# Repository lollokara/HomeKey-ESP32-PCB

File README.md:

<div align="center">

# HomeKey-ESP32-PCB

**A miniaturized, wall-mountable HomeKey reader board**

A custom PCB implementation of [rednblkx/HomeKey-ESP32](https://github.com/rednblkx/HomeKey-ESP32) that brings Apple HomeKey NFC unlocking into a form factor small enough to hide behind your existing wall plate.

</div>

## What is this?

This project is a **hardware redesign** of the excellent [HomeKey-ESP32](https://github.com/rednblkx/HomeKey-ESP32) firmware by [@rednblkx](https://github.com/rednblkx). Instead of using a separate development board wired to a breakout PN532 module, everything is integrated onto a single, compact PCB.

The board packs an **ESP32-C3** and an **NFC reader front-end with an on-board coaxial NFC antenna** into a footprint designed to fit inside a **European 503 (3-module) flush-mount wall box**. This lets you install a fully functional Apple HomeKey reader directly behind a standard wall plate — no external modules, no messy wiring.

## Key Highlights

- **All-in-one PCB** — ESP32-C3 + NFC front-end + coaxial antenna on a single board
- **Fits a European 503 plug slot** — designed for standard flush-mount wall boxes
- **Integrated coaxial NFC antenna** — tuned on-board antenna, no external coil needed
- **Runs the original HomeKey-ESP32 firmware** — full Apple HomeKey / HomeKit compatibility
- **Fully open hardware** — designed in **KiCad**, with schematics, layout, Gerbers and a 3D model included

## Get the Board

Don't want to fabricate it yourself? You can order the PCB directly from PCBWay:

**➡️ [ESP32 HomeKey on PCBWay](https://www.pcbway.com/project/shareproject/ESP32_Homekey_77a119d7.html)**

## Designed in KiCad

The entire board is designed with **[KiCad](https://www.kicad.org/)**, so the complete hardware source is open and editable. The repository includes:

- Hierarchical KiCad schematics (`Homekey.kicad_sch`, `ESP32.kicad_sch`, `NFC.kicad_sch`, `Power.kicad_sch`, `Square.kicad_sch`)
- KiCad PCB layout (`Homekey.kicad_pcb`) and project file (`Homekey.kicad_pro`)
- Exported schematic PDF (`Homekey.pdf`)
- Bill of Materials (`Homekey.xlsx`)
- A 3D model of the assembly (`Homekey 3D.step.zip`)

You can open the project directly in KiCad to review, modify, or re-fabricate the board.

## Repository Structure

```
HomeKey-ESP32-PCB/
├── Firmware/              # HomeKey-ESP32 firmware (based on the original repo)
├── Gerbers/               # Fabrication-ready Gerber files
├── ESP32.kicad_sch        # ESP32-C3 subsheet
├── NFC.kicad_sch          # NFC front-end + antenna subsheet
├── Power.kicad_sch        # Power supply subsheet
├── Square.kicad_sch       # Additional subsheet
├── Homekey.kicad_sch      # Top-level schematic
├── Homekey.kicad_pcb      # PCB layout
├── Homekey.kicad_pro      # KiCad project file
├── Homekey.pdf            # Schematic (PDF export)
├── Homekey.xlsx           # Bill of Materials
├── Homekey-job.gbrjob     # Gerber job file
├── Homekey 3D.step.zip    # 3D model of the board
├── Homekey-3D-render.png  # 3D render of the assembled board
└── README.md
```

## Getting Started

### 1. Get the Board

- **Buy it ready-made:** order the PCB directly from [PCBWay](https://www.pcbway.com/project/shareproject/ESP32_Homekey_77a119d7.html).
- **Fabricate it yourself:** use the ready-to-order files in the [`Gerbers`](Gerbers) folder with your preferred PCB fab house.
- Refer to `Homekey.xlsx` for the Bill of Materials and `Homekey.pdf` for the schematic.
- To modify the design first, open `Homekey.kicad_pro` in KiCad.

### 2. Flash the Firmware

The board runs the standard HomeKey-ESP32 firmware. The [`Firmware`](Firmware) folder contains a build based on the original repository.

```bash
# Install esptool (one-time setup)
pip install esptool

# Flash the firmware (replace YOUR_PORT)
esptool.py --port YOUR_PORT write_flash 0x0 firmware.factory.bin
```

> Prefer a GUI? Use the [browser-based flasher](https://espressif.github.io/esptool-js/) — no command line needed.

For firmware configuration, pairing, and usage, follow the official documentation:
- **Docs:** https://rednblkx.github.io/HomeKey-ESP32/
- **Upstream firmware:** https://github.com/rednblkx/HomeKey-ESP32

### 3. Install & Pair

1. Mount the board inside your 503 wall box behind the plate.
2. Connect to the device's setup WiFi AP and configure your WiFi + HomeKit setup code.
3. Pair with Apple Home and start unlocking with a tap of your iPhone or Apple Watch. 🎉

## Credits

- **[@rednblkx](https://github.com/rednblkx)** — creator of the original [HomeKey-ESP32](https://github.com/rednblkx/HomeKey-ESP32) firmware this board is built for
- **[@kormax](https://github.com/kormax)** — reverse-engineered the HomeKey NFC protocol
- **[@kupa22](https://github.com/kupa22)** — researched the HAP side of HomeKey

## License

This project is licensed under the **MIT License** — see the [LICENSE](LICENSE) file for details.

## Disclaimer

This project implements Apple HomeKey functionality through reverse engineering.

- **Not affiliated** with, nor condoned by, Apple Inc.
- **Use at your own risk** for security-critical applications.
- **Apple**, **iPhone**, and **Apple Watch** are trademarks of Apple Inc.
- **ESP32** is a trademark of Espressif Systems (Shanghai) Co., Ltd.

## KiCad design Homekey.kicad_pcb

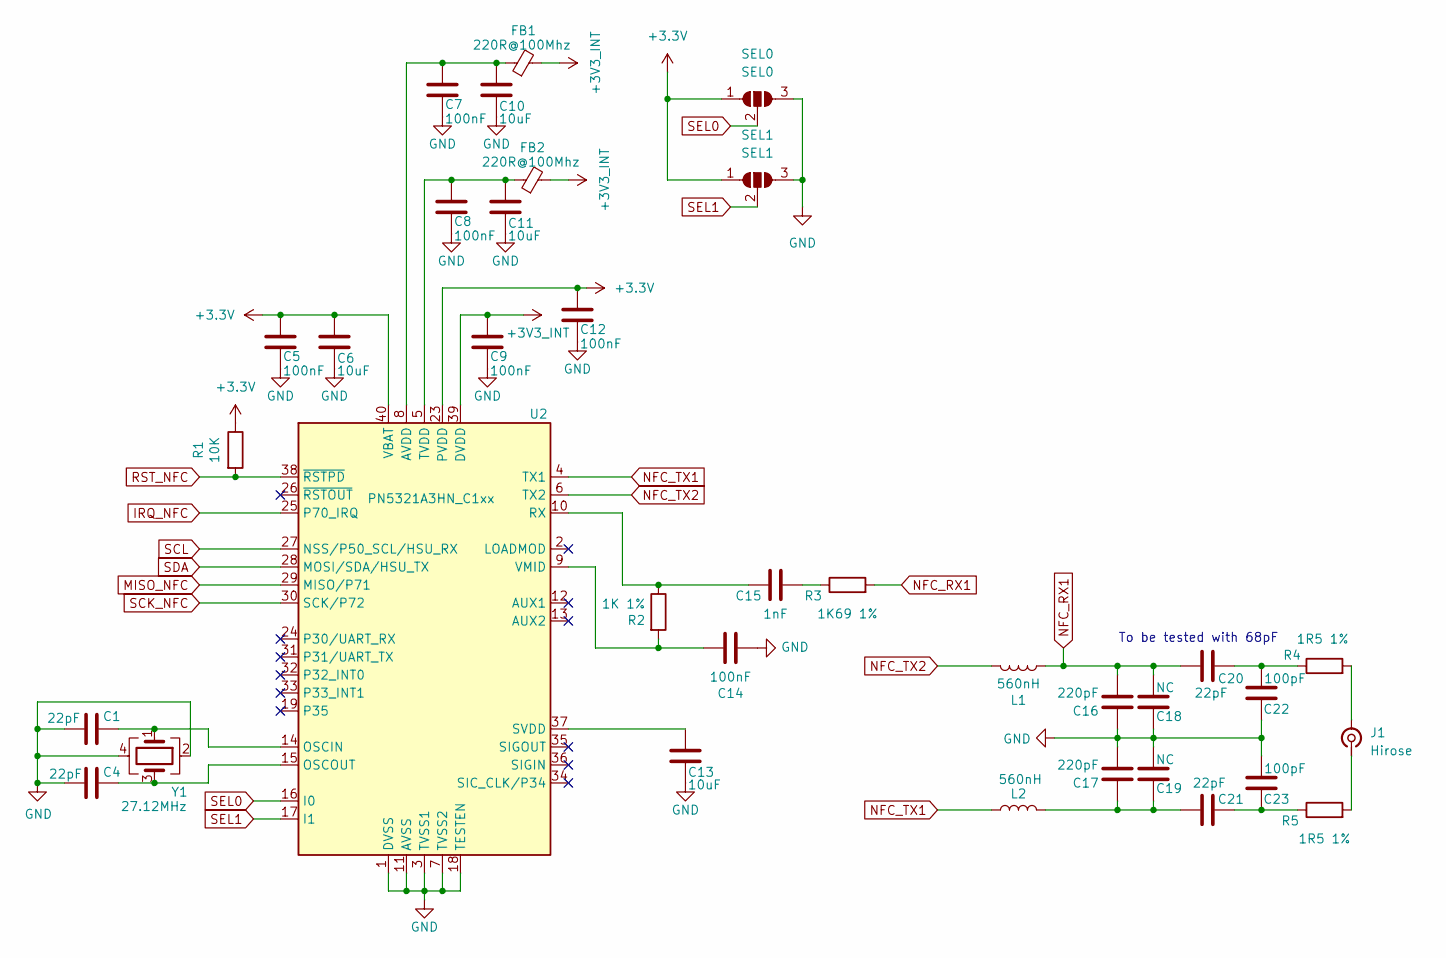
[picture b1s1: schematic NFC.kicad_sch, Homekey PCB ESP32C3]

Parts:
C1, C4: 22pF; C_0603_1608Metric; Part No 0603-22pF-50V
C5, C7, C8, C9, C12: 100nF; C_0603_1608Metric
C6, C10, C11, C13: 10uF; C_0805_2012Metric
C14: 100nF; C_0603_1608Metric; Part No 0603-100nF-25V
C15: 1nF; C_0603_1608Metric; Part No VJ0603A102GXAPW1BC
C16, C17: 220pF; C_0603_1608Metric; Part No 0603-220pF-50V
C18, C19: NC; C_0603_1608Metric
C20, C21: 22pF; C_0603_1608Metric; Part No 0603N220F500CT
C22, C23: 100pF; C_0603_1608Metric; Part No 0603-100pF-50V
FB1, FB2: 220R@100Mhz; L_0603_1608Metric
J1: Hirose; U.FL_Hirose_U.FL-R-SMT-1_Vertical
L1, L2: 560nH; L_0805_2012Metric; Part No LQW2UASR56G00L
R1: 10K; R_0603_1608Metric; Part No 0603-10K
R2: 1K 1%; R_0603_1608Metric; Part No CRCW06031K00FKEAC
R3: 1K69 1%; R_0603_1608Metric; Part No RC0603FR-101K69L
R4, R5: 1R5 1%; R_0603_1608Metric; Part No CRCW06031R50FKEA
SEL0: SEL0; SolderJumper-3_P2.0mm_Open_TrianglePad1.0x1.5mm
SEL1: SEL1; SolderJumper-3_P2.0mm_Open_TrianglePad1.0x1.5mm
U2: PN5321A3HN_C1xx; HVQFN-40-1EP_6x6mm_P0.5mm_EP4.1x4.1mm
Y1: 27.12MHz; Crystal_SMD_3225-4Pin_3.2x2.5mm; Part No ABM81-27.120MHZ-10-B1U-T3

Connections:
+3.3V: C5.2, C6.1, C12.2, R1.1, SEL0.1 (A), SEL1.1 (A), U2.23 (PVDD), U2.40 (VBAT); also elsewhere on the board
+3V3_INT: C9.2, FB1.2, FB2.2, U2.39 (DVDD)
GND: C1.2, C4.2, C5.1, C6.2, C7.1, C8.1, C9.1, C10.2, C11.2, C12.1, C13.2, C14.2, C16.1, C17.1, C18.1, C19.2, C22.1, C23.2, SEL0.3 (B), SEL1.3 (B), U2.1 (DVSS), U2.3 (TVSS1), U2.7 (TVSS2), U2.11 (AVSS), U2.18 (TESTEN), U2.41 (AVSS), Y1.2, Y1.4; also elsewhere on the board
IRQ_NFC: U2.25 (P70_IRQ); also elsewhere on the board
MISO_NFC: U2.29 (MISO/P71); also elsewhere on the board
NFC_RX1: C16.2, C18.2, C20.1, L1.1, R3.2
NFC_TX1: L2.1, U2.4 (TX1)
NFC_TX2: L1.2, U2.6 (TX2)
unnamed: C15.2, R3.1
unnamed: C17.2, C19.1, C21.1, L2.2
unnamed: C20.2, C22.2, R4.1
unnamed: C21.2, C23.1, R5.1
unnamed: J1.2 (Ext), R4.2
unnamed: J1.1 (In), R5.2
unnamed: C7.2, C10.1, FB1.1, U2.8 (AVDD)
unnamed: C1.1, U2.14 (OSCIN), Y1.1
unnamed: C4.1, U2.15 (OSCOUT), Y1.3
unnamed: C15.1, R2.1, U2.10 (RX)
unnamed: C13.1, U2.37 (SVDD)
unnamed: C8.2, C11.1, FB2.1, U2.5 (TVDD)
unnamed: C14.1, R2.2, U2.9 (VMID)
RST_NFC: R1.2, U2.38 (~RSTPD); also elsewhere on the board
SCK_NFC: U2.30 (SCK/P72); also elsewhere on the board
SCL: U2.27 (NSS/P50_SCL/HSU_RX); also elsewhere on the board
SDA: U2.28 (MOSI/SDA/HSU_TX); also elsewhere on the board
SEL0: SEL0.2 (C), U2.16 (I0)
SEL1: SEL1.2 (C), U2.17 (I1)

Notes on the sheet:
To be tested with 68pF

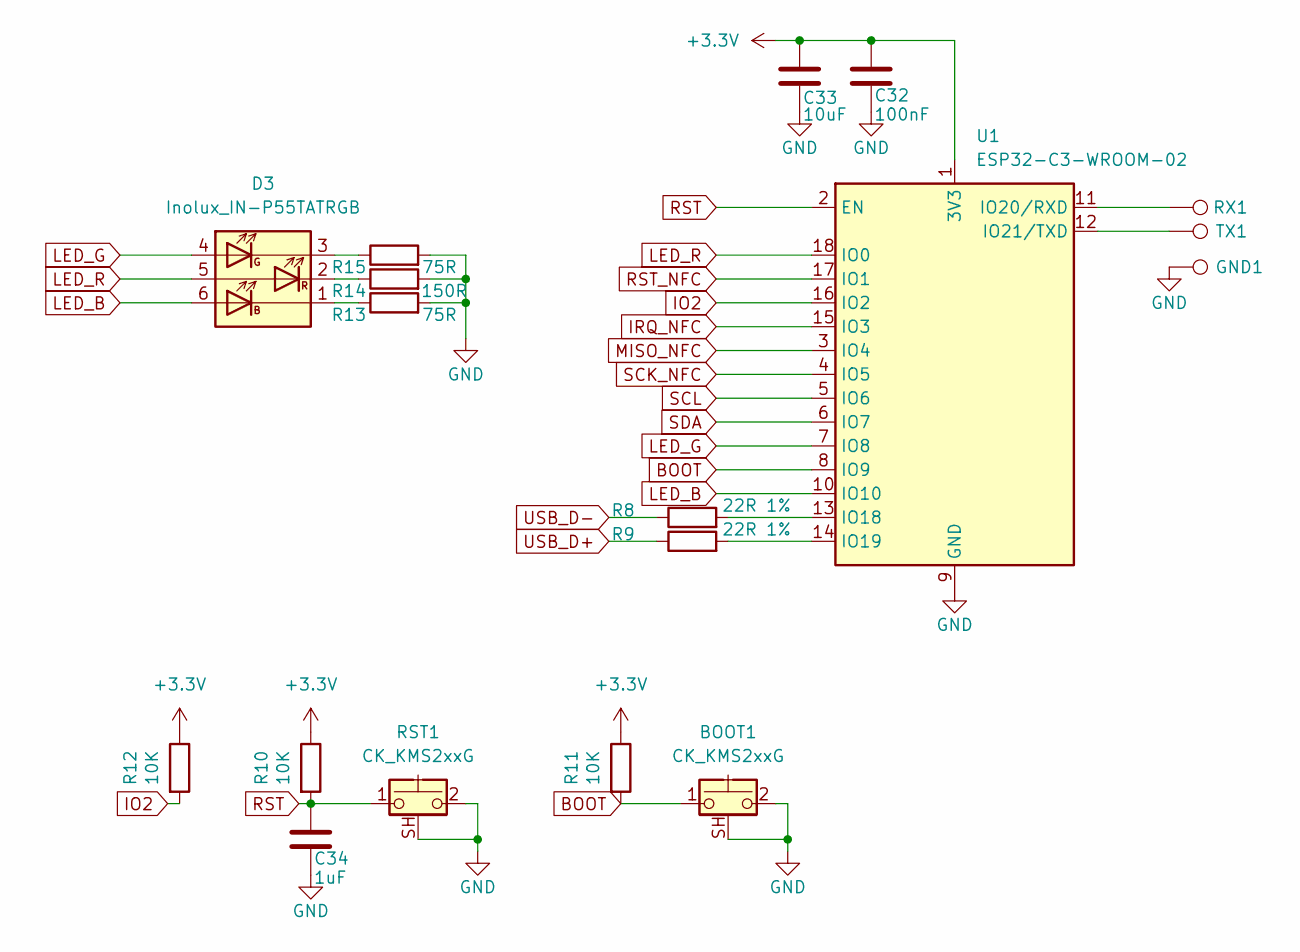
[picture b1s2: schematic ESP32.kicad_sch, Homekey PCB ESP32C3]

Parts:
BOOT1: CK_KMS2xxG; SW_SPST_CK_KMS2xxGP
C32: 100nF; C_0603_1608Metric
C33: 10uF; C_0805_2012Metric
C34: 1uF; C_0603_1608Metric
D3: Inolux_IN-P55TATRGB; LED_Inolux_IN-P55TATRGB_PLCC6_5.0x5.5mm_P1.8mm
GND1: TestPoint; TestPoint_THTPad_1.5x1.5mm_Drill0.7mm
R8, R9: 22R 1%; R_0603_1608Metric; Part No RC0603FR-1022RL
R10, R11, R12: 10K; R_0603_1608Metric; Part No 0603-10K
R13, R15: 75R; R_0603_1608Metric; Part No RC0603FR-0775RL
R14: 150R; R_0603_1608Metric; Part No RC0603JR-07160RL
RST1: CK_KMS2xxG; SW_SPST_CK_KMS2xxGP
RX1: TestPoint; TestPoint_THTPad_1.5x1.5mm_Drill0.7mm
TX1: TestPoint; TestPoint_THTPad_1.5x1.5mm_Drill0.7mm
U1: ESP32-C3-WROOM-02

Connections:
+3.3V: C32.2, C33.1, R10.1, R11.1, R12.1, U1.1 (3V3); also elsewhere on the board
BOOT: BOOT1.1, R11.2, U1.8 (IO9)
GND: BOOT1.2, BOOT1.SH (B), C32.1, C33.2, C34.1, GND1.1, R13.2, R14.2, R15.2, RST1.2, RST1.SH (B), U1.9 (GND), U1.19 (GND); also elsewhere on the board
IO2: R12.2, U1.16 (IO2)
IRQ_NFC: U1.15 (IO3); also elsewhere on the board
LED_B: D3.6 (AB), U1.10 (IO10)
LED_G: D3.4 (AG), U1.7 (IO8)
LED_R: D3.5 (AR), U1.18 (IO0)
MISO_NFC: U1.3 (IO4); also elsewhere on the board
unnamed: D3.1 (KB), R13.1
unnamed: D3.3 (KG), R15.1
unnamed: D3.2 (KR), R14.1
unnamed: R8.2, U1.13 (IO18)
unnamed: R9.2, U1.14 (IO19)
unnamed: RX1.1, U1.11 (IO20/RXD)
unnamed: TX1.1, U1.12 (IO21/TXD)
RST: C34.2, R10.2, RST1.1, U1.2 (EN)
RST_NFC: U1.17 (IO1); also elsewhere on the board
SCK_NFC: U1.4 (IO5); also elsewhere on the board
SCL: U1.5 (IO6); also elsewhere on the board
SDA: U1.6 (IO7); also elsewhere on the board
USB_D+: R9.1; also elsewhere on the board
USB_D-: R8.1; also elsewhere on the board

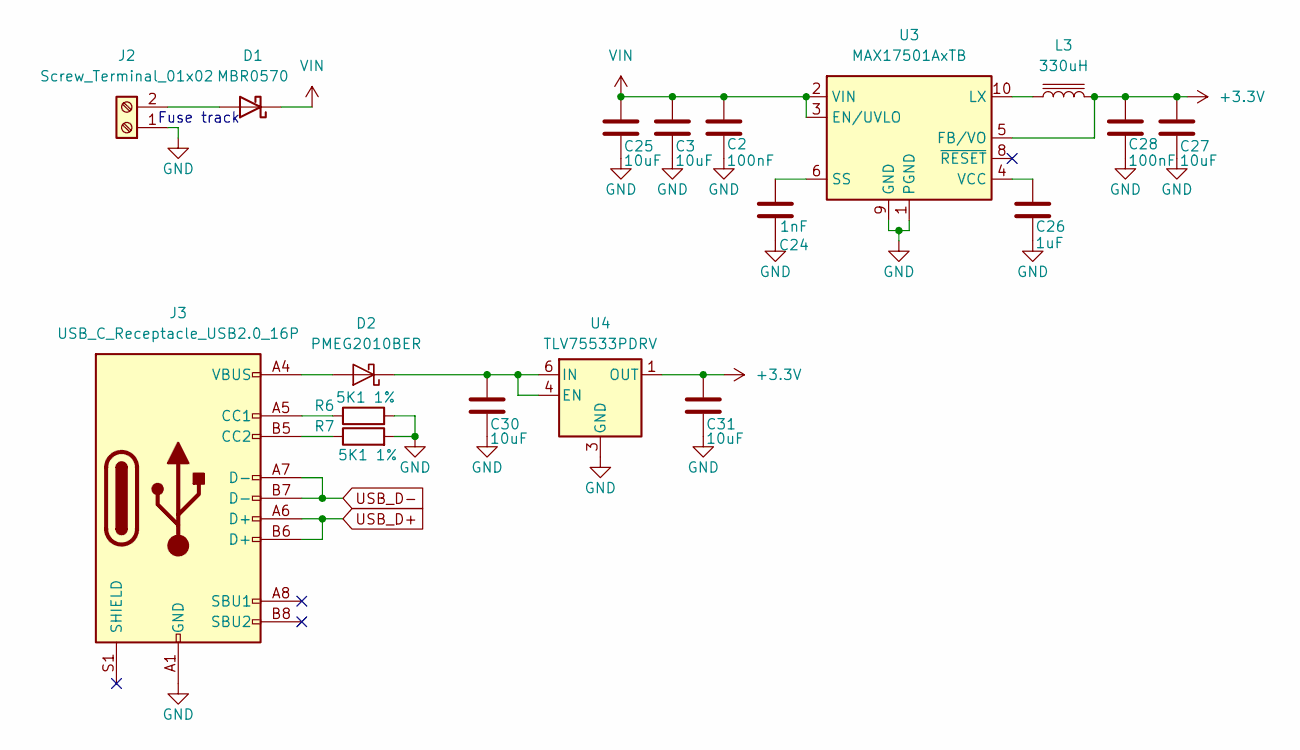
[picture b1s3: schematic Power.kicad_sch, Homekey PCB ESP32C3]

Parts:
C2, C28: 100nF; C_0603_1608Metric
C3, C25, C27, C30, C31: 10uF; C_0805_2012Metric
C24: 1nF; C_0603_1608Metric; Part No VJ0603A102GXAPW1BC
C26: 1uF; C_0603_1608Metric
D1: MBR0570; Fuseholder_Littelfuse_Nano2_157x
D2: PMEG2010BER; Nexperia_CFP3_SOD-123W
J2: Screw_Terminal_01x02; TerminalBlock_Phoenix_MPT-0,5-2-2.54_1x02_P2.54mm_Horizontal
J3: USB_C_Receptacle_USB2.0_16P; USB_C_Receptacle_GCT_USB4110
L3: 330uH; L_Bourns_SRN6045TA
R6, R7: 5K1 1%; R_0603_1608Metric; Part No RC0603FR-105K1L
U3: MAX17501AxTB; TDFN-10-1EP_2x3mm_P0.5mm_EP0.9x2mm
U4: TLV75533PDRV; WSON-6-1EP_2x2mm_P0.65mm_EP1x1.6mm

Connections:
+3.3V: C27.1, C28.2, C31.1, L3.2, U3.5 (FB/VO), U4.1 (OUT); also elsewhere on the board
GND: C2.1, C3.2, C24.1, C25.2, C26.1, C27.2, C28.1, C30.2, C31.2, J2.1, J3.A1 (GND), J3.A12 (GND), J3.B1 (GND), J3.B12 (GND), R6.2, R7.2, U3.1 (PGND), U3.9 (GND), U3.11 (GND), U4.3 (GND), U4.7 (GND); also elsewhere on the board
unnamed: D1.2 (A), J2.2
unnamed: D2.2 (A), J3.A4 (VBUS), J3.A9 (VBUS), J3.B4 (VBUS), J3.B9 (VBUS)
unnamed: C30.1, D2.1 (K), U4.4 (EN), U4.6 (IN)
unnamed: J3.A5 (CC1), R6.1
unnamed: J3.B5 (CC2), R7.1
unnamed: L3.1, U3.10 (LX)
unnamed: C24.2, U3.6 (SS)
unnamed: C26.2, U3.4 (VCC)
USB_D+: J3.A6 (D+), J3.B6 (D+); also elsewhere on the board
USB_D-: J3.A7 (D-), J3.B7 (D-); also elsewhere on the board
VIN: C2.2, C3.1, C25.1, D1.1 (K), U3.2 (VIN), U3.3 (EN/UVLO)

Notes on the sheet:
Fuse track

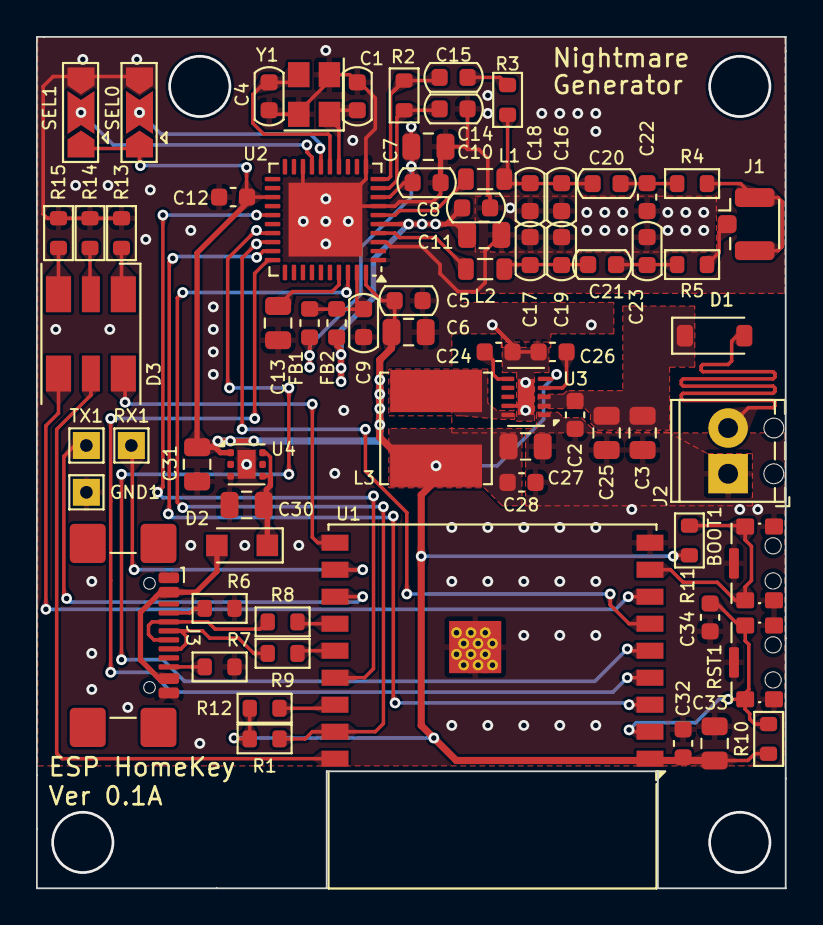
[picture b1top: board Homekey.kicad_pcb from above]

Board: 2 copper layers, 41.6 x 47.3 mm, 71 parts (0 on the bottom side), 51 nets.

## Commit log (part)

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2024-07-03 Initial Push :)
2024-07-03 Concluded ESP32 + Power
    still need to have a look around for errors
2024-07-03 Added Revs + PDF
2024-07-09 Start of layout
2024-07-09 Finished rev A PCB V 0.1
2024-07-12 Adding gerbers + BOM
2024-08-02 Added centroid files for PNP
2024-08-21 Added Teardops to the various connection, repoured polys, updated gerbers
2024-08-23 Added 3D Model
2024-09-24 Fixed SS problem, bumped C24 to 3300pF
2024-10-01 Adding Firmware based on the original repo

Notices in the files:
README.md:
License: MIT
